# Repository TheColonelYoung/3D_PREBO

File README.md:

# **3D_PrEBo**
<br />

This project is 3D printer expansion board.  Add more fan controllers, TMC2130 wiring support, induction probe voltage convertor, LED lighting (supports WS1812).

This board was designed for best compatibility with MKS GEN L, but is compatible for example with BIGTREETECH SKR 1.1.

### **Board features**

- Stepdown regulator - from up to 35V to 12V
    - can by bypassed by jumper, if you have 12V power supply by solder jumper
    - minimal volatage for regulator is 15V
    - based on L5973D (up to 2A)

- Advanced fan controll
    - you can controll up to 8 fans
    - 1 fan is 4 pin, others are 3 pin with additional transistor
    - speed input for fan is from motherboard (EXP_X connectors)
    - one of fans can be used as regulated fan for hotend cooling (temperature dependent cooling)
    - Fan voltage can be selected from , Vin, 12V, 5V via solder bridges
    - Expected fan distibution: 1x Motherboard fan, 2x part cooling fans, 1x hotend cooling fan, 4 fans for other usage (maybe motors)
    - input signal for fans can be chain, one signal can drive more fans

- Probe connector
    - serve as input from inductive probe
    - Voltage divider, designed as 24V -> 5V

- TMC2130 wiring
    - helps to keep wiring simple and clean
    - holes in board for simple wiring and better airflow around cables
    - 4 pin connectors
    - if motherboard didn't have enough pins, in Marlin 2.0, can be TMC2130 enabled via SPI, so EN pin for driver can be used as Chip select fro SPI
    
- LED light
    - means as print part lighting
    - selectable voltage (5V or 12 V) by solder jumper

- 5 in one connector
    - Onboard RJ-45 connectors and UTP cable (8-wires)
    - As HUB is used second board mounted on printer head
    - Fans, Led outputs and both outputs (6in1 and separe)
    - Pins:
        - 1x GND, 1x 12V,
        - 3x FAN
        - 1x X Endstop (or 5V Z probe if on hat isn't X endstop)
        - 2x LED lights

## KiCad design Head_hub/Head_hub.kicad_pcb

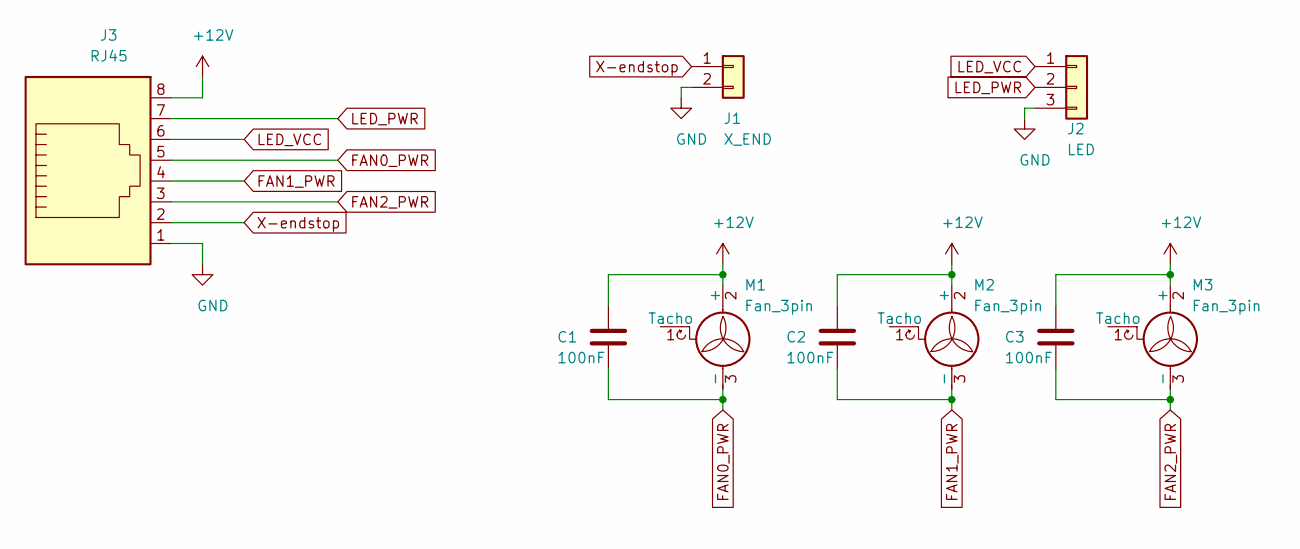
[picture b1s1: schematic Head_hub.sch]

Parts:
C1, C2, C3: 100nF; C_0603_1608Metric
J1: X_END; JST_XH_B02B-XH-A_1x02_P2.50mm_Vertical
J2: LED; JST_XH_B03B-XH-A_1x03_P2.50mm_Vertical
J3: RJ45; RJ45_Amphenol_54602-x08_Horizontal
M1, M2, M3: Fan_3pin; FanPinHeader_1x03_P2.54mm_Vertical

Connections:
+12V: C1.1, C2.1, C3.1, J3.8, M1.2 (+), M2.2 (+), M3.2 (+)
FAN0_PWR: C1.2, J3.5, M1.3 (-)
FAN1_PWR: C2.2, J3.4, M2.3 (-)
FAN2_PWR: C3.2, J3.3, M3.3 (-)
GND: J1.2, J2.3, J3.1
LED_PWR: J2.2, J3.7
LED_VCC: J2.1, J3.6
X-endstop: J1.1, J3.2

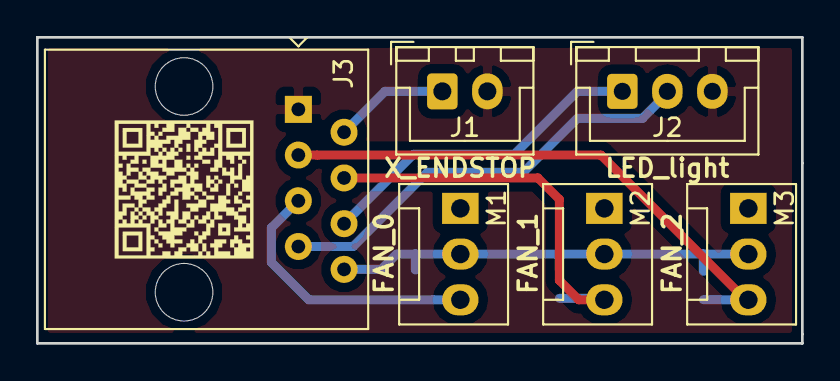
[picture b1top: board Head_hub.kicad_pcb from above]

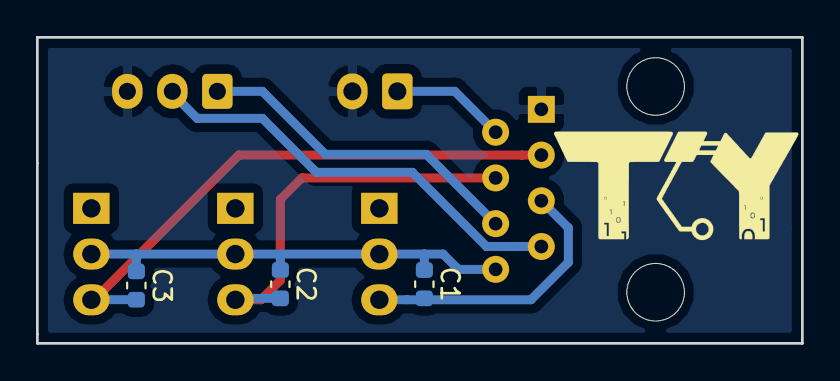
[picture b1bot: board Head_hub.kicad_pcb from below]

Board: 2 copper layers, 42.5 x 17.0 mm, 9 parts (3 on the bottom side), 8 nets.

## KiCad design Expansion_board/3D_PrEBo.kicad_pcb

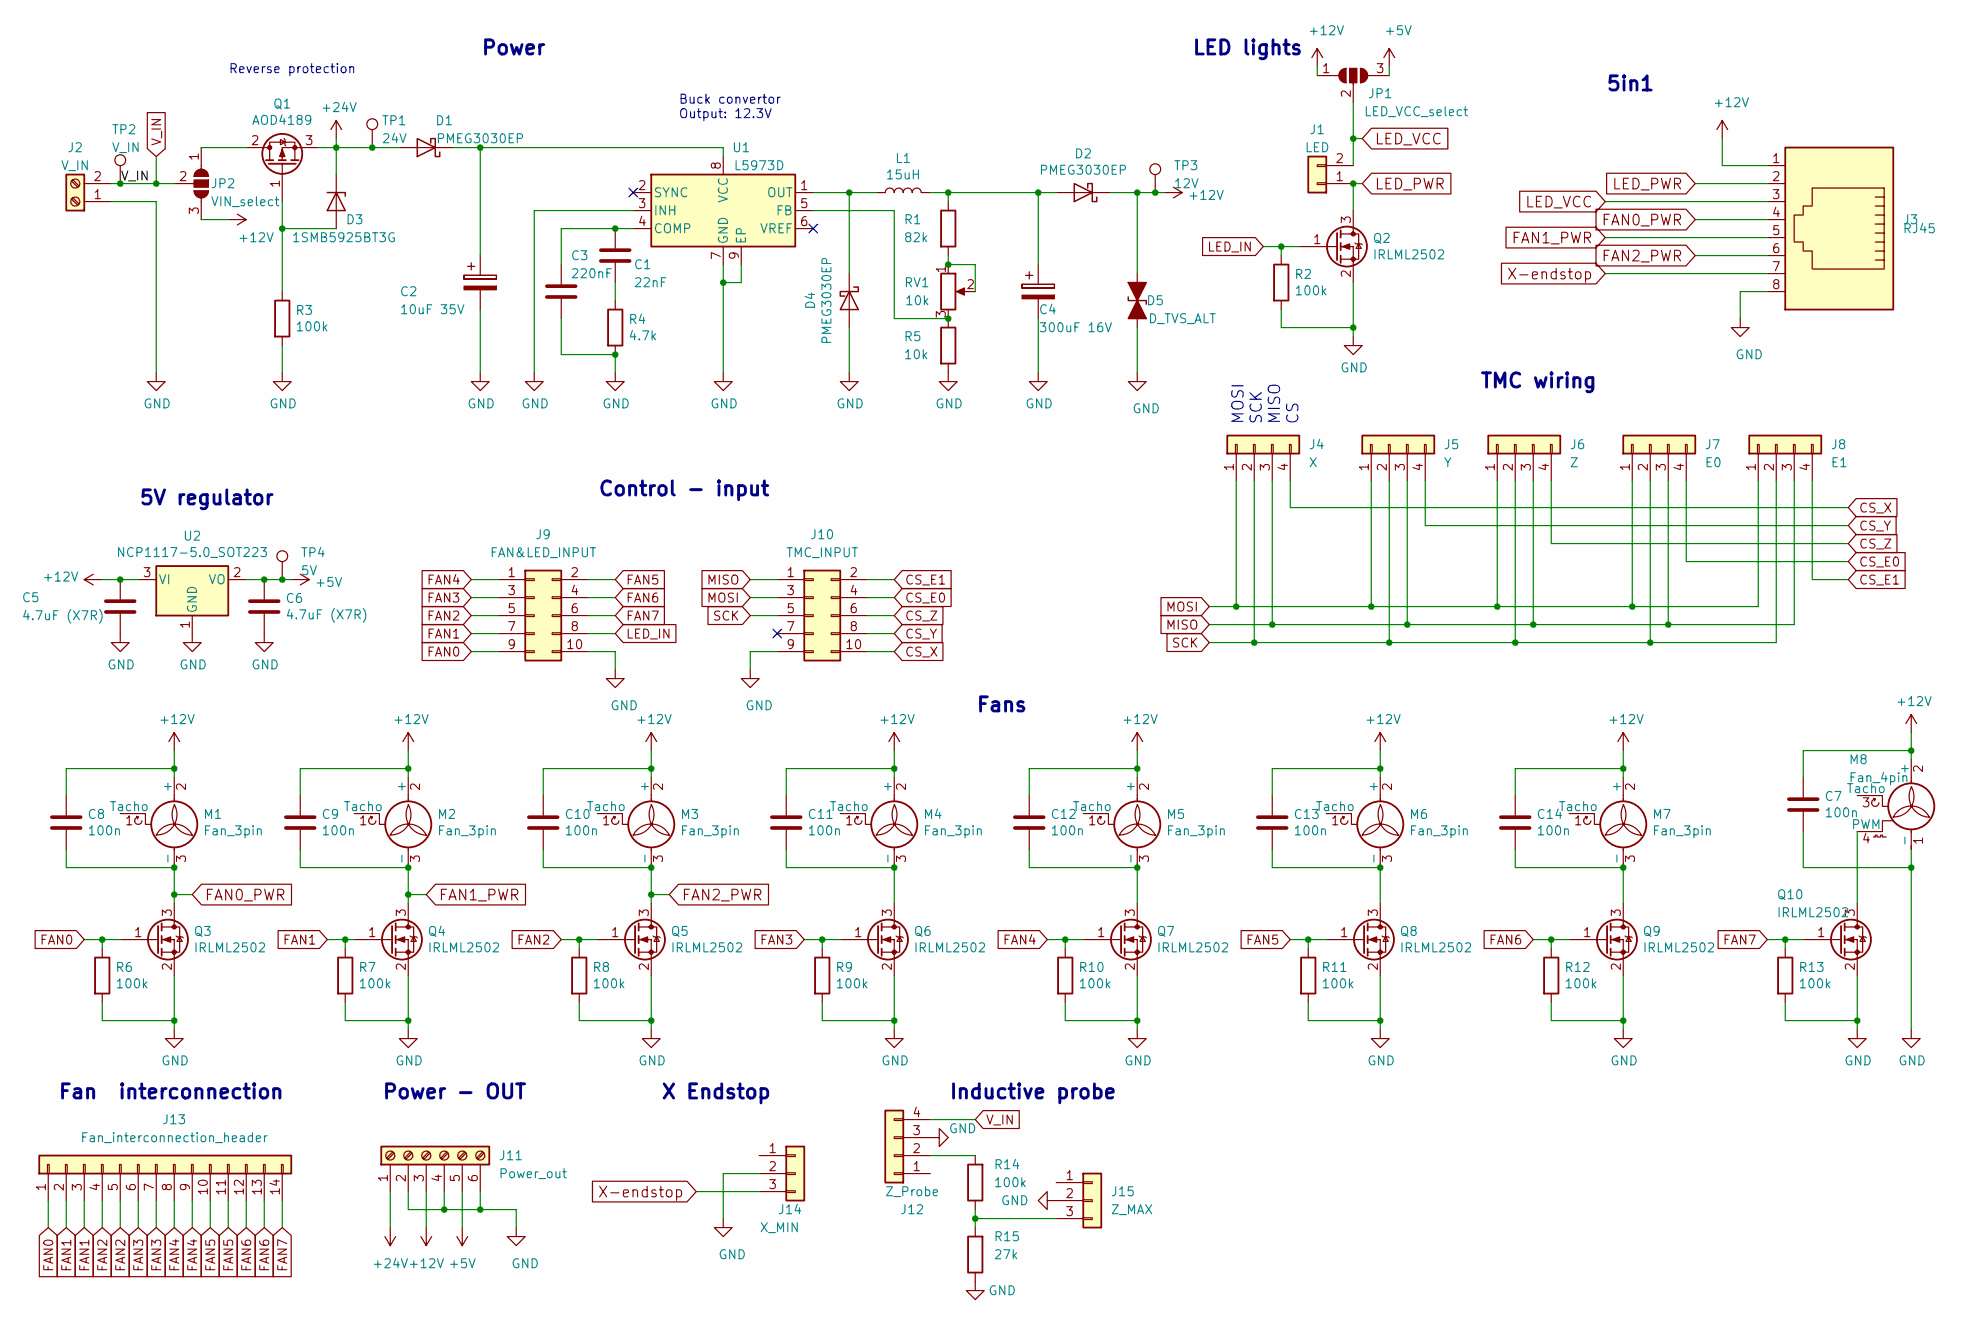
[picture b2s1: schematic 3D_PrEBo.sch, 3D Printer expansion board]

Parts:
C1: 22nF; C_0603_1608Metric
C2: 10uF 35V; C_2816_7142Metric_Pad3.20x4.45mm_HandSolder
C3: 220nF; C_0603_1608Metric
C4: 300uF 16V; CP_Elec_8x10.5
C5, C6: 4.7uF (X7R); C_0805_2012Metric
C7, C8, C9, C10, C11, C12, C13, C14: 100n; C_0603_1608Metric
D1, D2, D4: PMEG3030EP; D_SMB
D3: 1SMB5925BT3G; D_SMB
D5: D_TVS_ALT; D_SMA
J1: LED; JST_XH_B02B-XH-A_1x02_P2.50mm_Vertical
J2: V_IN; TerminalBlock_Phoenix_MKDS-1,5-2_1x02_P5.00mm_Horizontal
J3: RJ45; RJ45_Amphenol_54602-x08_Horizontal
J4: X; PinHeader_1x04_P2.54mm_Horizontal
J5: Y; PinHeader_1x04_P2.54mm_Horizontal
J6: Z; PinHeader_1x04_P2.54mm_Horizontal
J7: E0; PinHeader_1x04_P2.54mm_Horizontal
J8: E1; PinHeader_1x04_P2.54mm_Horizontal
J9: FAN&LED_INPUT; IDC-Header_2x05_P2.54mm_Horizontal
J10: TMC_INPUT; IDC-Header_2x05_P2.54mm_Horizontal
J11: Power_out; TerminalBlock_Phoenix_MKDS-1,5-6_1x06_P5.00mm_Horizontal
J12: Z_Probe; JST_XH_B04B-XH-A_1x04_P2.50mm_Vertical
J13: Fan_interconnection_header; PinHeader_1x14_P2.54mm_Vertical
J14: X_MIN; JST_XH_S03B-XH-A-1_1x03_P2.50mm_Horizontal
J15: Z_MAX; JST_XH_S03B-XH-A-1_1x03_P2.50mm_Horizontal
JP1: LED_VCC_select; SolderJumper-3_P1.3mm_Open_RoundedPad1.0x1.5mm
JP2: VIN_select; SolderJumper-3_P1.3mm_Open_RoundedPad1.0x1.5mm
L1: 15uH; L_Neosid_Ms85
M1, M2, M3, M4, M5, M6, M7: Fan_3pin; JST_XH_S03B-XH-A_1x03_P2.50mm_Horizontal
M8: Fan_4pin; JST_XH_S04B-XH-A_1x04_P2.50mm_Horizontal
Q1: AOD4189; TO-252-2
Q2, Q3, Q4, Q5, Q6, Q7, Q8, Q9, Q10: IRLML2502; TSOT-23
R1: 82k; R_0603_1608Metric
R2, R3, R6, R7, R8, R9, R10, R11, R12, R13, R14: 100k; R_0603_1608Metric
R4: 4.7k; R_0603_1608Metric
R5: 10k; R_0603_1608Metric
R15: 27k; R_0603_1608Metric
RV1: 10k; Potentiometer_Bourns_3214J_Horizontal
TP1: 24V; TestPoint_THTPad_D1.5mm_Drill0.7mm
TP2: V_IN; TestPoint_THTPad_D1.5mm_Drill0.7mm
TP3: 12V; TestPoint_THTPad_D1.5mm_Drill0.7mm
TP4: 5V; TestPoint_THTPad_D1.5mm_Drill0.7mm
U1: L5973D; HTSOP-8-1EP_3.9x4.9mm_P1.27mm_EP2.4x3.2mm
U2: NCP1117-5.0_SOT223; SOT-223-3_TabPin2

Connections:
+5V: C6.1, J11.5, JP1.3 (B), TP4.1, U2.2 (VO)
+12V: C5.1, C7.1, C8.1, C9.1, C10.1, C11.1, C12.1, C13.1, C14.1, D2.1 (K), D5.2 (A2), J3.1, J11.3, JP1.1 (A), JP2.3 (B), M1.2 (+), M2.2 (+), M3.2 (+), M4.2 (+), M5.2 (+), M6.2 (+), M7.2 (+), M8.2 (+), TP3.1, U2.3 (VI)
+24V: D1.2 (A), D3.1 (K), J11.1, Q1.3 (S), TP1.1
CS_E0: J7.4, J10.4
CS_E1: J8.4, J10.2
CS_X: J4.4, J10.10
CS_Y: J5.4, J10.8
CS_Z: J6.4, J10.6
FAN0: J9.9, J13.1, Q3.1 (G), R6.1
FAN0_PWR: C8.2, J3.4, M1.3 (-), Q3.3 (D)
FAN1: J9.7, J13.2, J13.3, Q4.1 (G), R7.1
FAN1_PWR: C9.2, J3.5, M2.3 (-), Q4.3 (D)
FAN2: J9.5, J13.4, J13.5, Q5.1 (G), R8.1
FAN2_PWR: C10.2, J3.6, M3.3 (-), Q5.3 (D)
FAN3: J9.3, J13.6, J13.7, Q6.1 (G), R9.1
FAN4: J9.1, J13.8, J13.9, Q7.1 (G), R10.1
FAN5: J9.2, J13.10, J13.11, Q8.1 (G), R11.1
FAN6: J9.4, J13.12, J13.13, Q9.1 (G), R12.1
FAN7: J9.6, J13.14, Q10.1 (G), R13.1
GND: C2.2, C3.2, C4.2, C5.2, C6.2, C7.2, D4.2 (A), D5.1 (A1), J2.1, J3.8, J9.10, J10.9, J11.2, J11.4, J11.6, J12.3, J14.2, J15.2, M8.1 (-), Q2.2 (S), Q3.2 (S), Q4.2 (S), Q5.2 (S), Q6.2 (S), Q7.2 (S), Q8.2 (S), Q9.2 (S), Q10.2 (S), R2.2, R3.2, R4.2, R5.2, R6.2, R7.2, R8.2, R9.2, R10.2, R11.2, R12.2, R13.2, R15.1, U1.3 (INH), U1.7 (GND), U1.9 (EP), U2.1 (GND)
LED_IN: J9.8, Q2.1 (G), R2.1
LED_PWR: J1.1, J3.2, Q2.3 (D)
LED_VCC: J1.2, J3.3, JP1.2 (C)
MISO: J4.3, J5.3, J6.3, J7.3, J8.3, J10.1
MOSI: J4.1, J5.1, J6.1, J7.1, J8.1, J10.3
unnamed: C1.1, C3.1, U1.4 (COMP)
unnamed: C1.2, R4.1
unnamed: C2.1, D1.1 (K), U1.8 (VCC)
unnamed: C4.1, D2.2 (A), L1.2, R1.1
unnamed: C11.2, M4.3 (-), Q6.3 (D)
unnamed: C12.2, M5.3 (-), Q7.3 (D)
unnamed: C13.2, M6.3 (-), Q8.3 (D)
unnamed: C14.2, M7.3 (-), Q9.3 (D)
unnamed: D3.2 (A), Q1.1 (G), R3.1
unnamed: D4.1 (K), L1.1, U1.1 (OUT)
unnamed: J12.2, R14.2
unnamed: J15.3, R14.1, R15.2
unnamed: JP2.1 (A), Q1.2 (D)
unnamed: M8.4 (PWM), Q10.3 (D)
unnamed: R1.2, RV1.1, RV1.2
unnamed: R5.1, RV1.3, U1.5 (FB)
SCK: J4.2, J5.2, J6.2, J7.2, J8.2, J10.5
V_IN: J2.2, J12.4, JP2.2 (C), TP2.1
X-endstop: J3.7, J14.3

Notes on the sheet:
Reverse protection
Buck convertor Output: 12.3V
5V regulator
Fan interconnection
Inductive probe
TMC wiring
MOSI SCK MISO CS
Fans
Power
5in1
LED lights
Power - OUT
X Endstop
Control - input

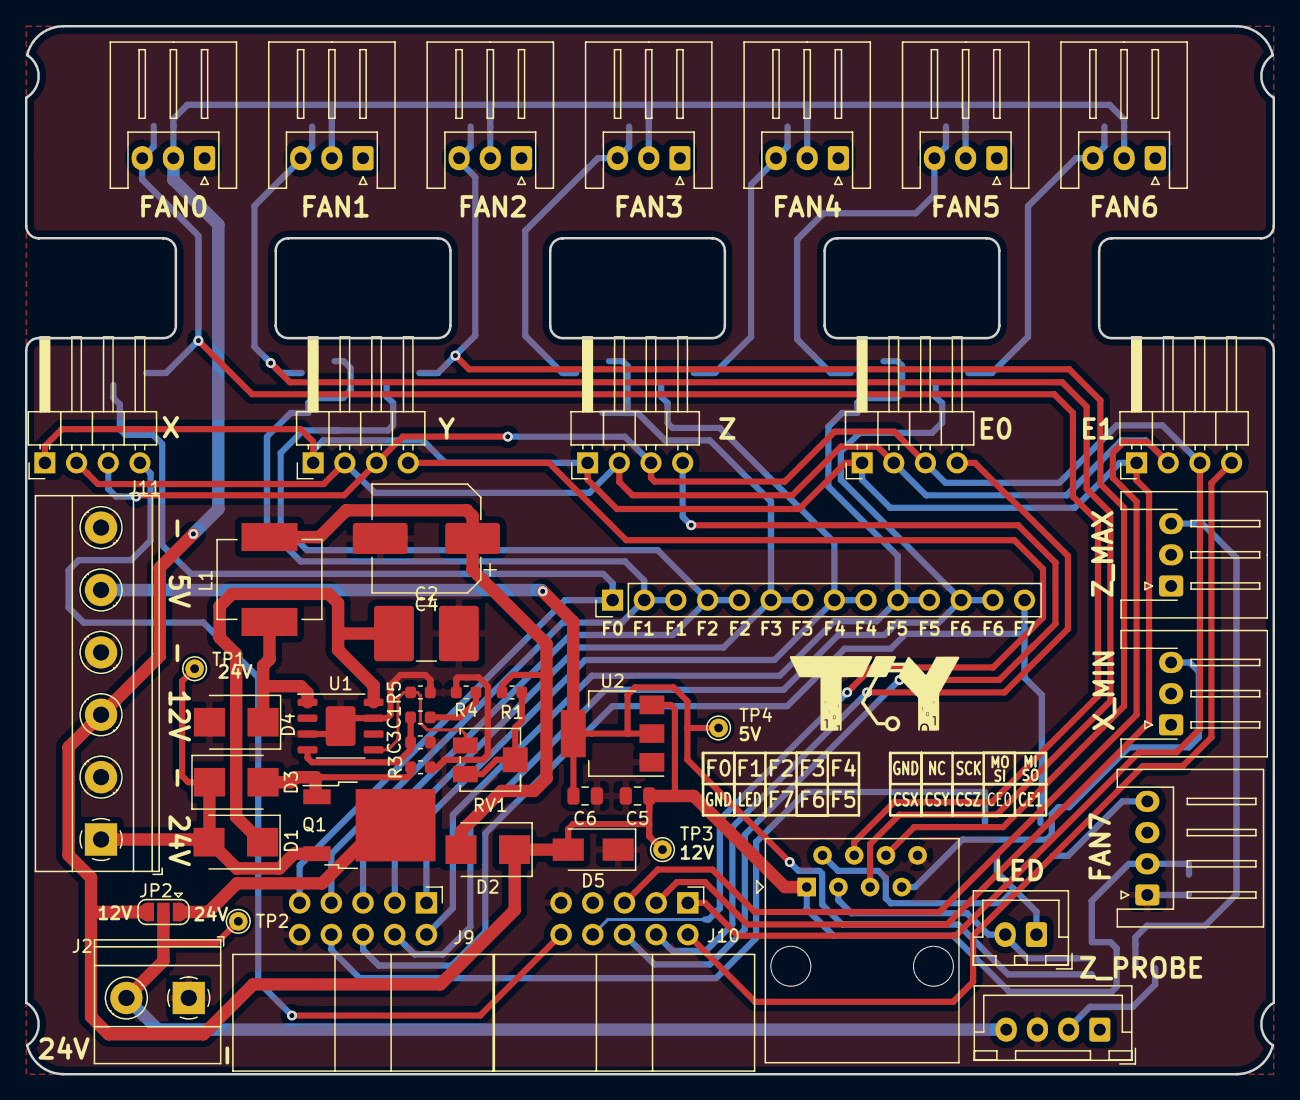
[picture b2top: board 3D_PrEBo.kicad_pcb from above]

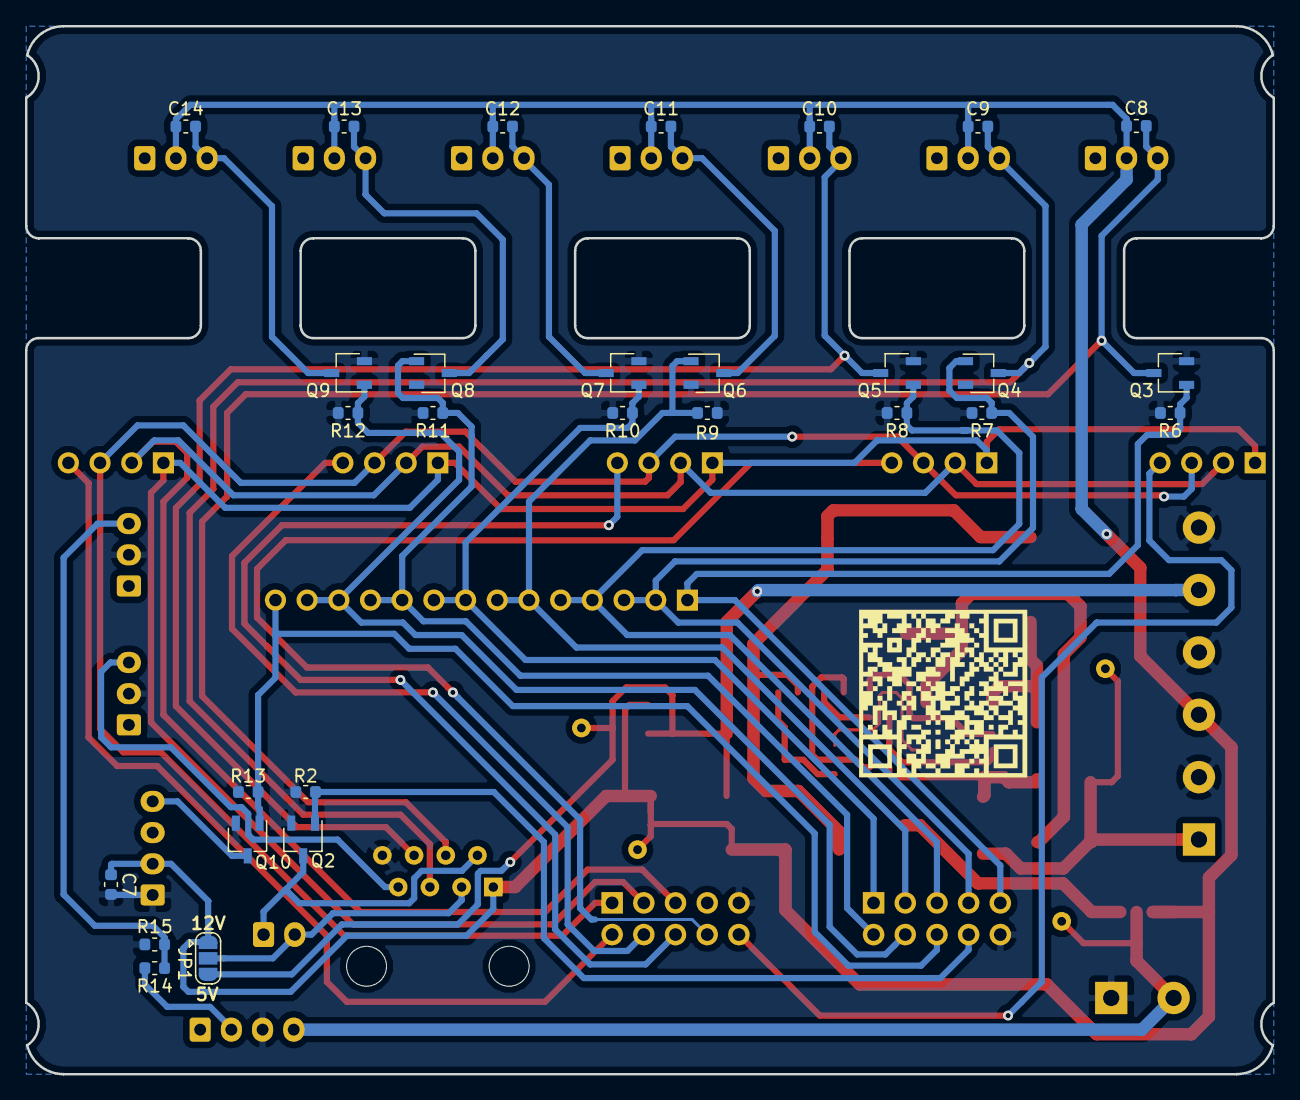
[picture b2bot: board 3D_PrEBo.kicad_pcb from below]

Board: 2 copper layers, 100.0 x 84.0 mm, 77 parts (29 on the bottom side), 44 nets.

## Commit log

2019-02-04 Add license, update specification in README.md
    Add board features: power management, fan controll, 6in1 connector, TMC2130.
2019-02-06 Updated README: change 6in1 to 5in1, other minor changes
2019-02-06 Schematic: Expansion board schematic, first draft
    TODO: inductive probe, Buck converter voltage settings
2019-02-06 Schematic: Add inductive probe and set voltage of buck converter
2019-02-06 Schematic: Add schematic in pdf, minor part shifting in schema
2019-02-06 Schema: Head_HUB: Initial schema and package assign
2019-02-06 Schema: Update part labels, Rewrite project description
2019-02-06 Head_HUB: PCB: Routing done
2019-02-06 Expansion_board: PCB: Add PCB outlines, position some parts on PCB
2019-02-07 Expansion_board: PCB: Place all parts, routing of voltage regulator
    Change horizontal fan connector to vertical.
    Pour cooper planes on both sides.
2019-02-07 Expansiopn_board: PCB: Routing done, Silk screen in progress
2019-02-08 Expansion_board: PCB: Rotate FAN transistors, update bottom silk screen
2019-02-08 Expansion_board: PCB: Fix some design limitations, move endstop connector
2019-02-10 Expansion_board: Schema: Change in buck convertor capacitors, add transil
    change capacitors to correct packages and voltages
    add transil to convertor output as overvoltage protection
2019-02-10 Expansion_board: PCB: Add trnasil, reroute capacitors
2019-02-11 Expansion_board: PCB: Update logo position
2019-02-11 Expansion_board: PCB: Updated silkscreen for power connectors
2019-02-11 Expansion_board: Add test points for voltages
2019-02-11 Expansion_board: Generate gerber data for fabrication
2019-02-11 Expansion_board: PCB: Add QR code with link to GitHub repository
2019-02-11 Expansion_board: Gerber: Add .zip with gerber files, removed unnecessary non-ziped gerber files
2019-02-11 Head_HUB: PCB: Add QR code with link to GitHub repository
2019-02-11 Head_HUB: Gerber: Add .zip with gerber files for fabrications

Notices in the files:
README.md:
Licence Creative Commons
